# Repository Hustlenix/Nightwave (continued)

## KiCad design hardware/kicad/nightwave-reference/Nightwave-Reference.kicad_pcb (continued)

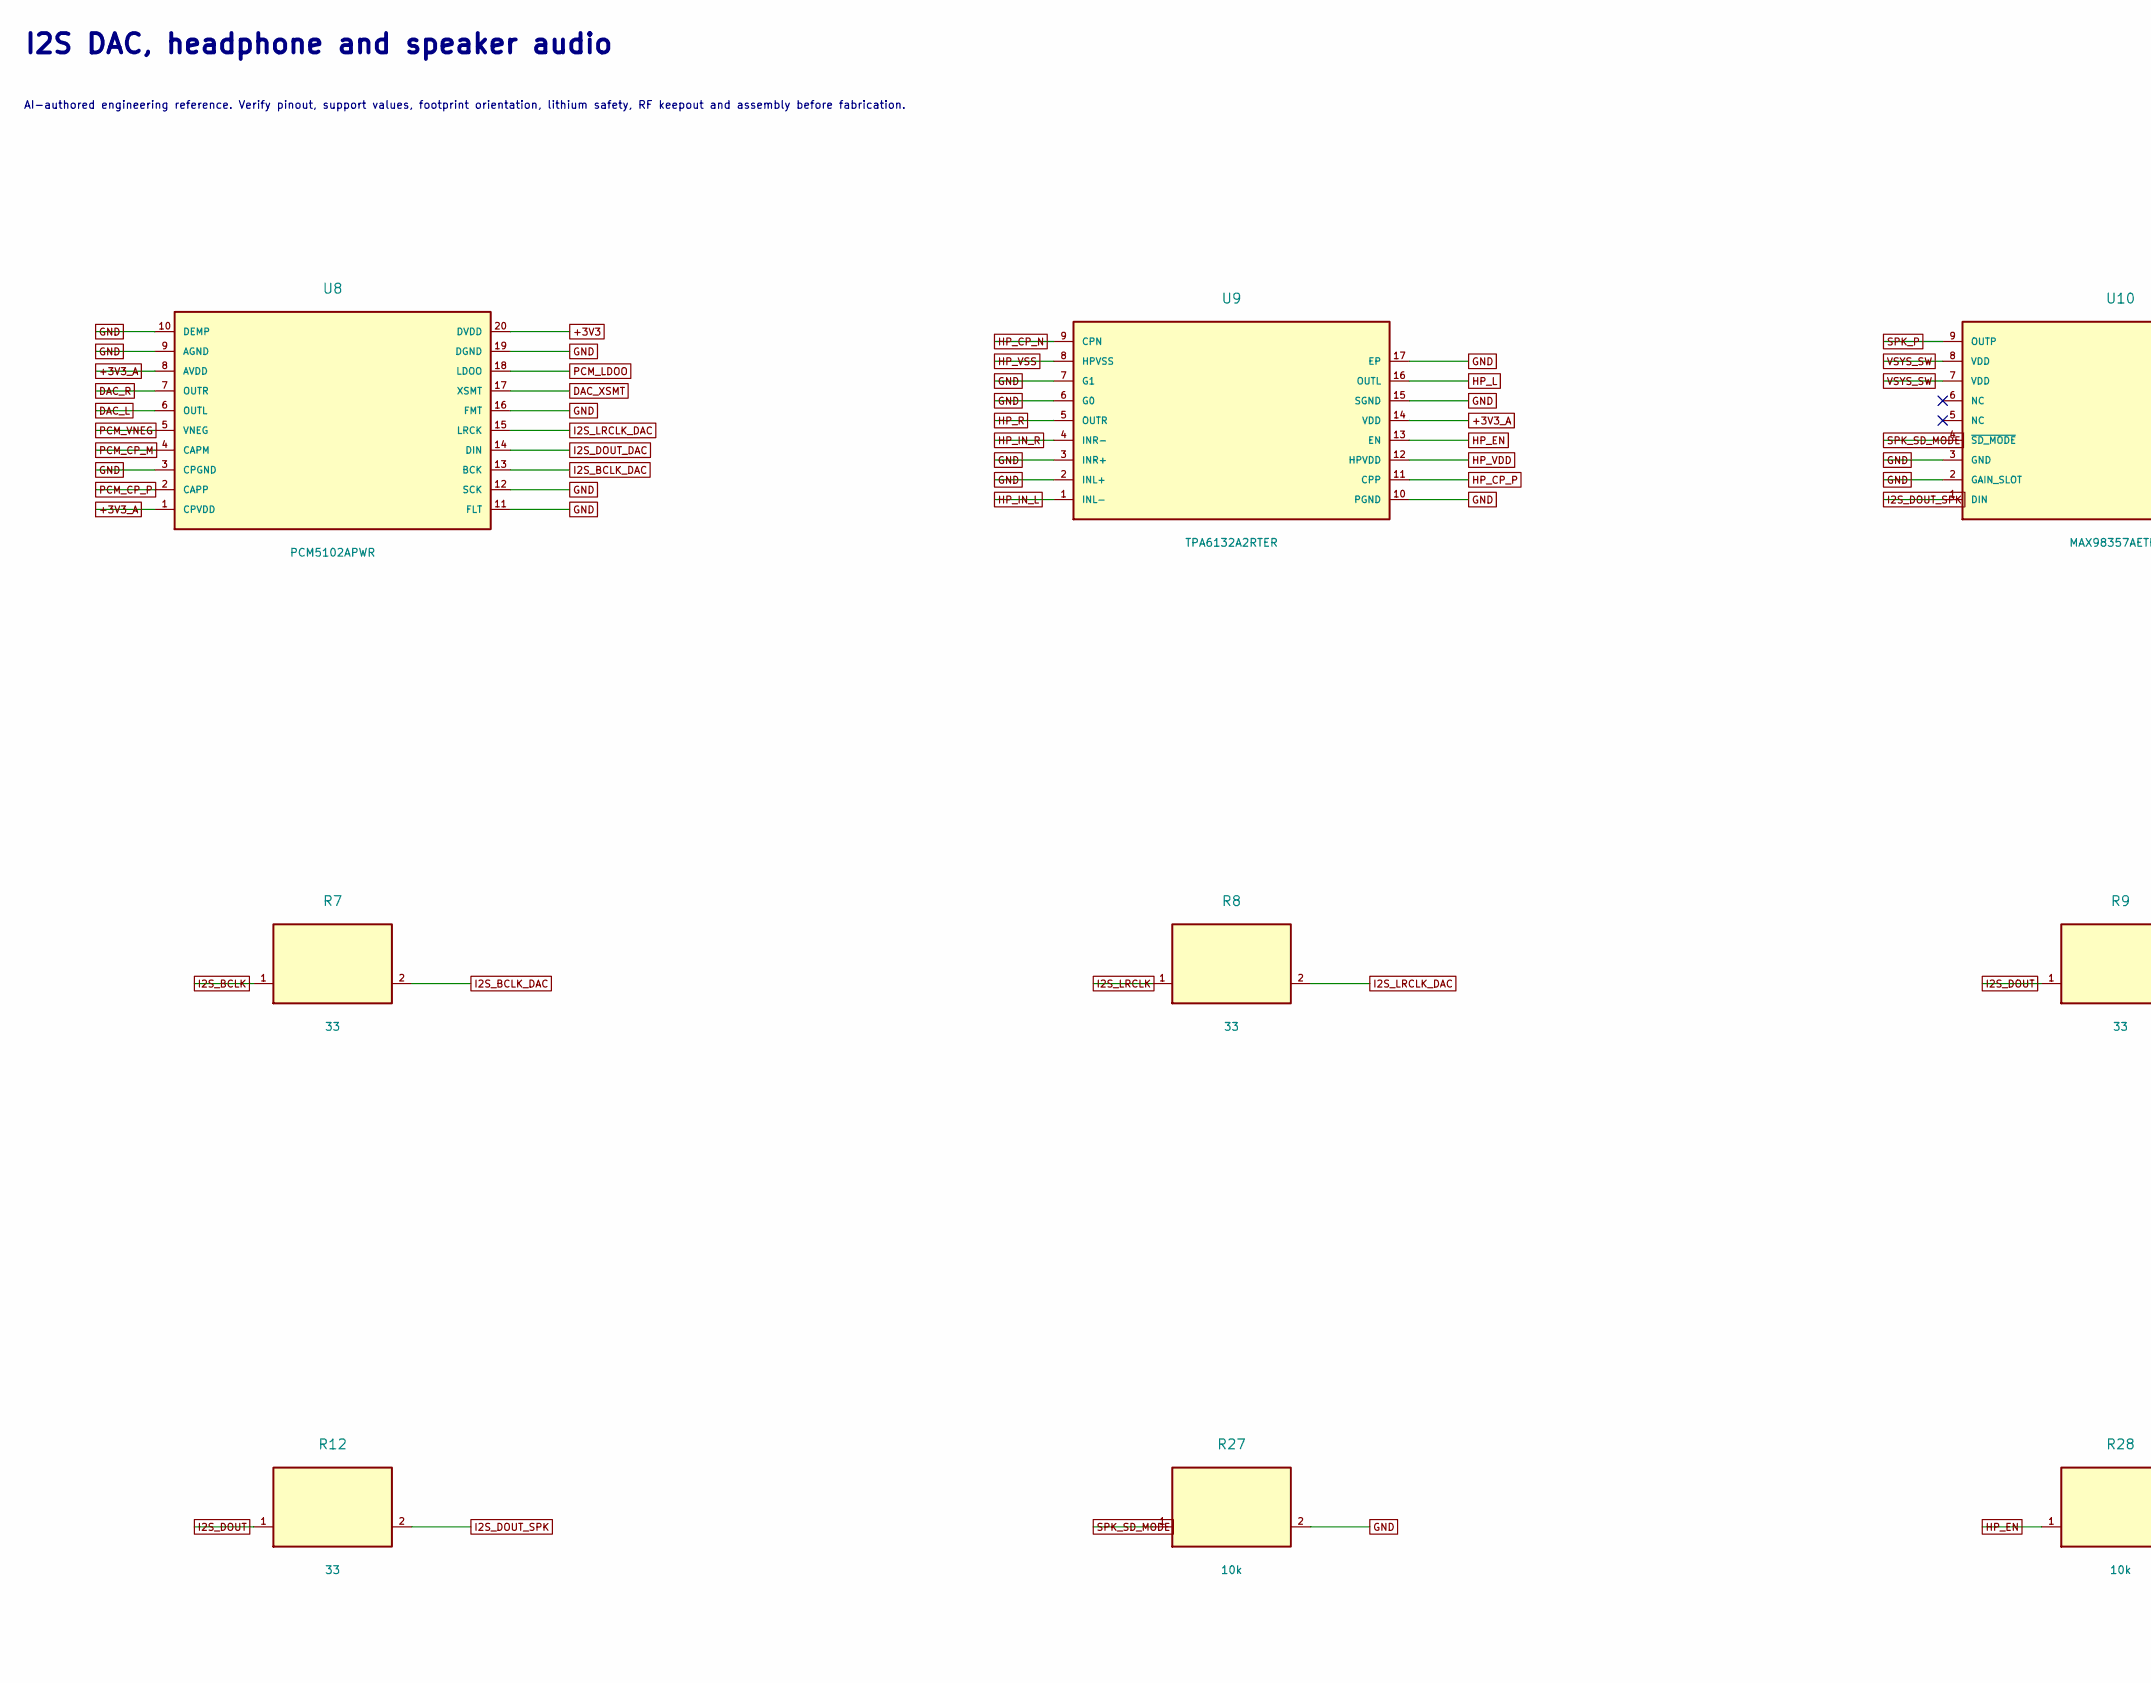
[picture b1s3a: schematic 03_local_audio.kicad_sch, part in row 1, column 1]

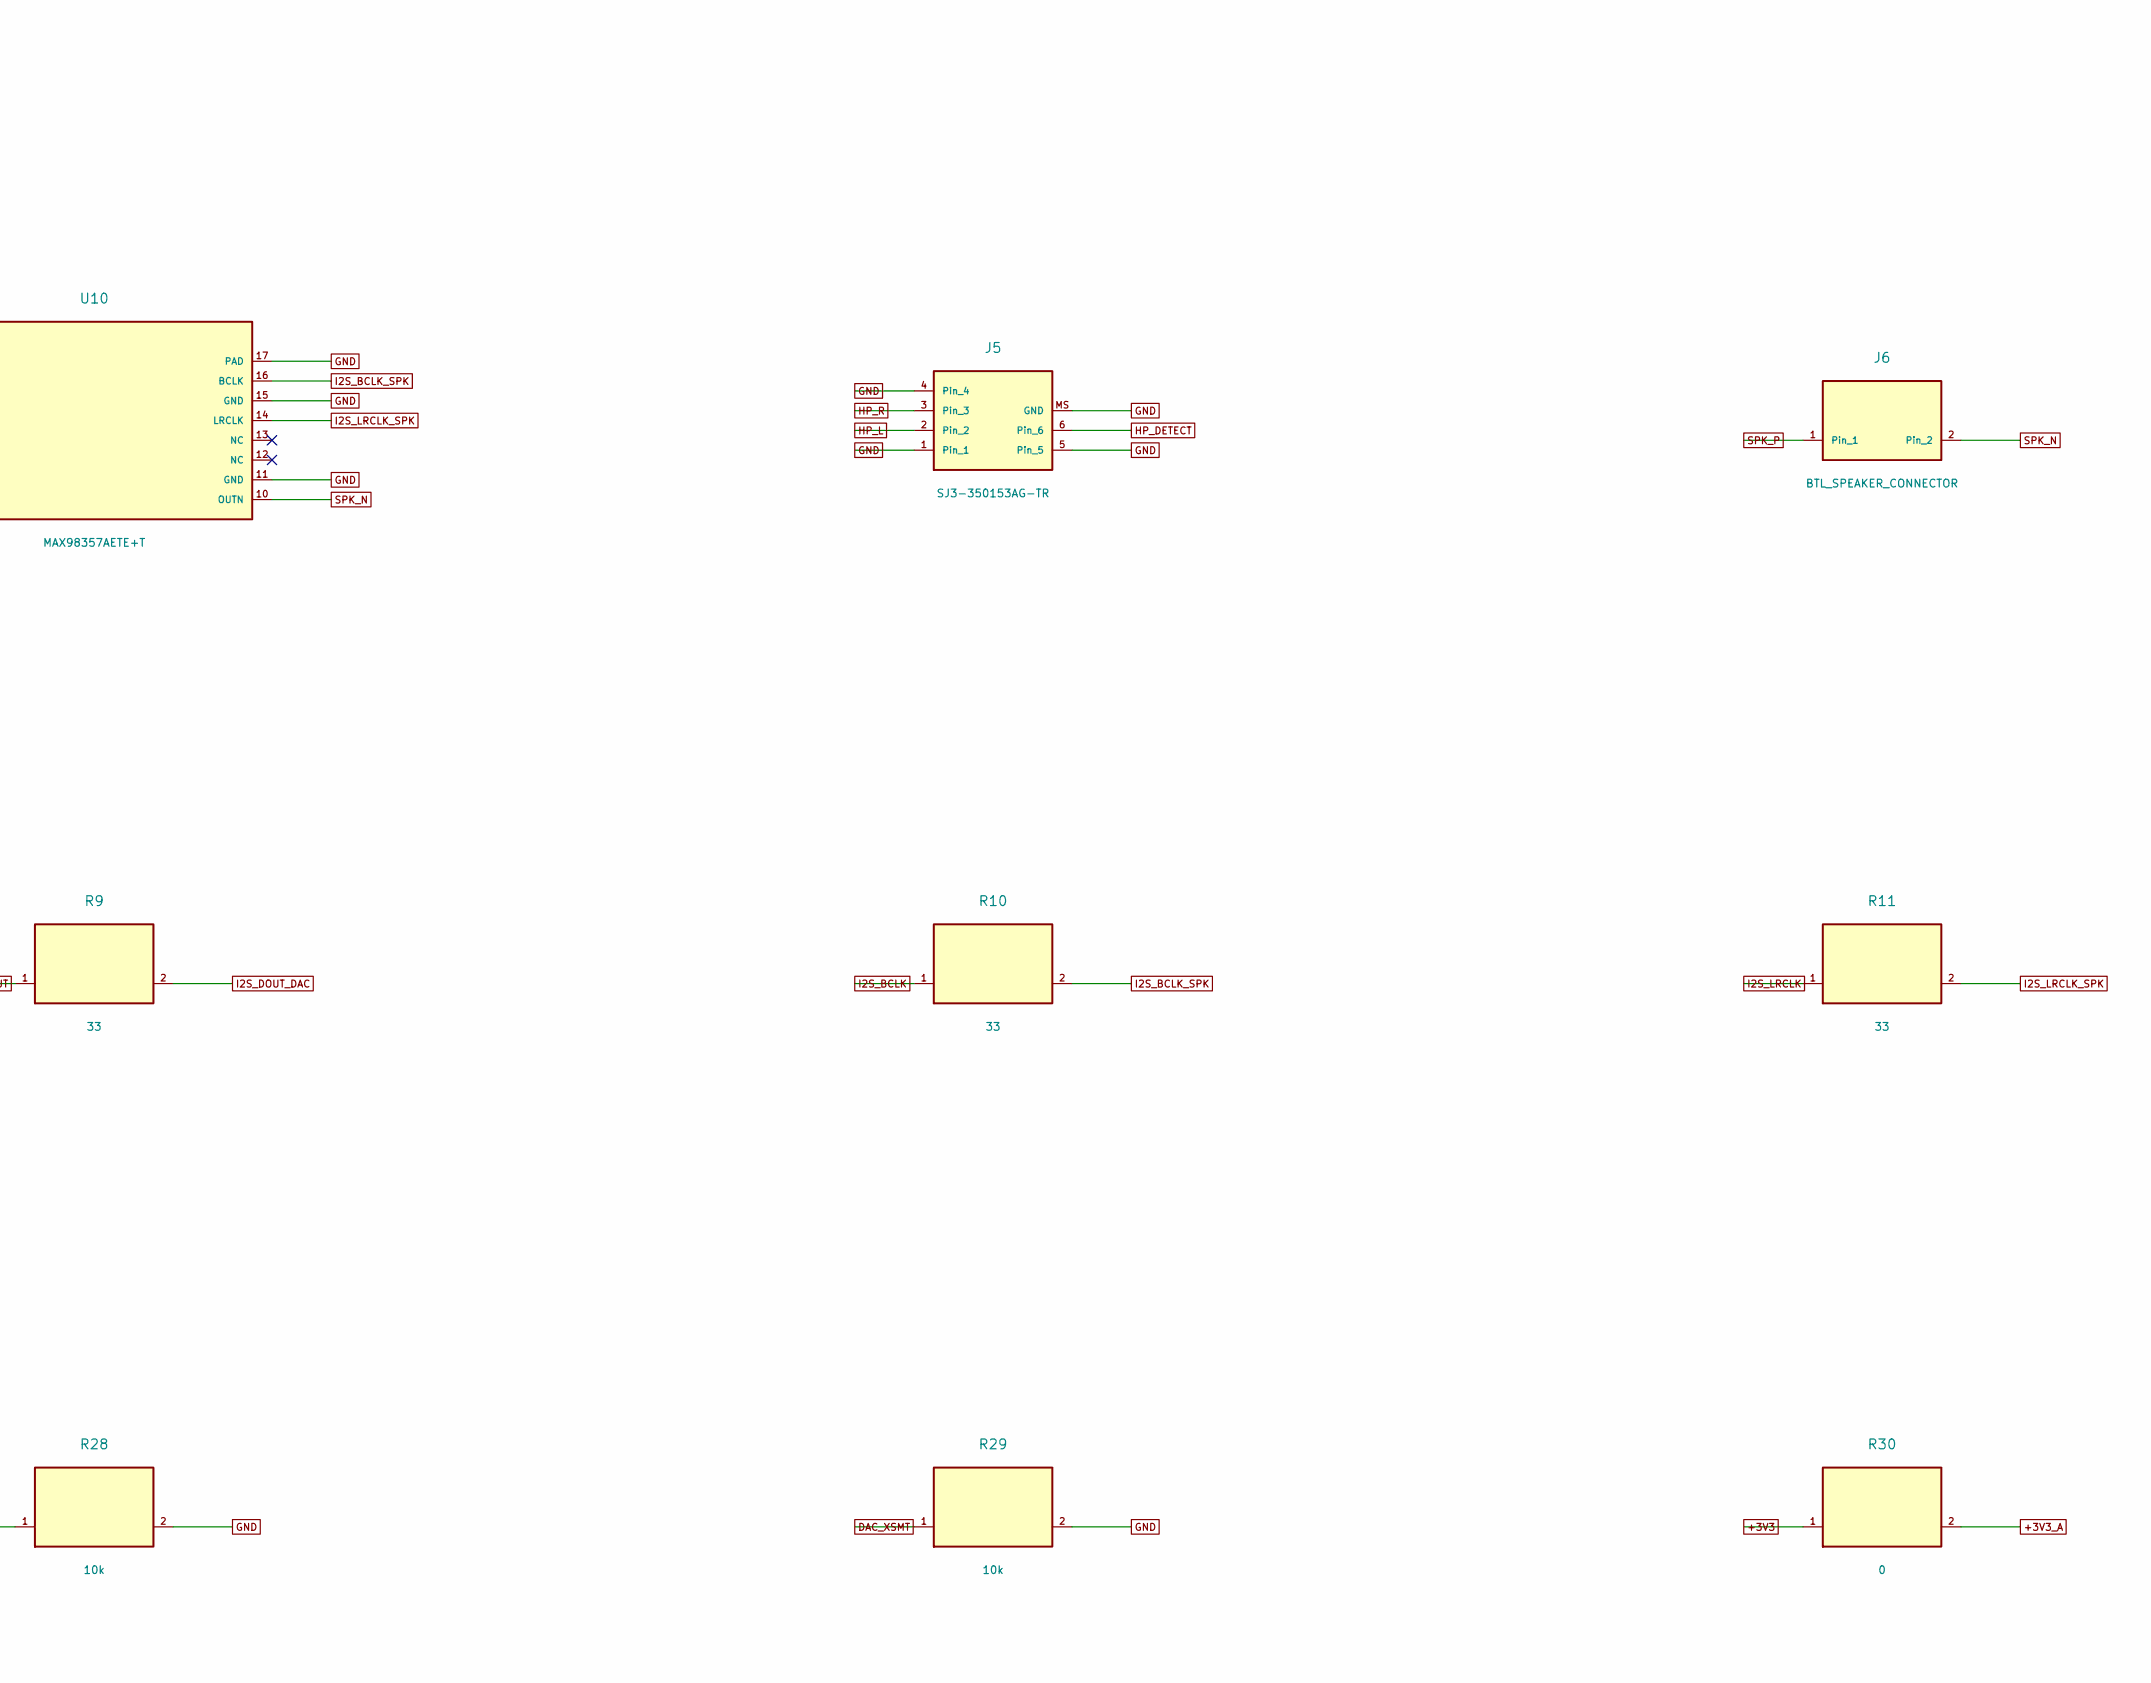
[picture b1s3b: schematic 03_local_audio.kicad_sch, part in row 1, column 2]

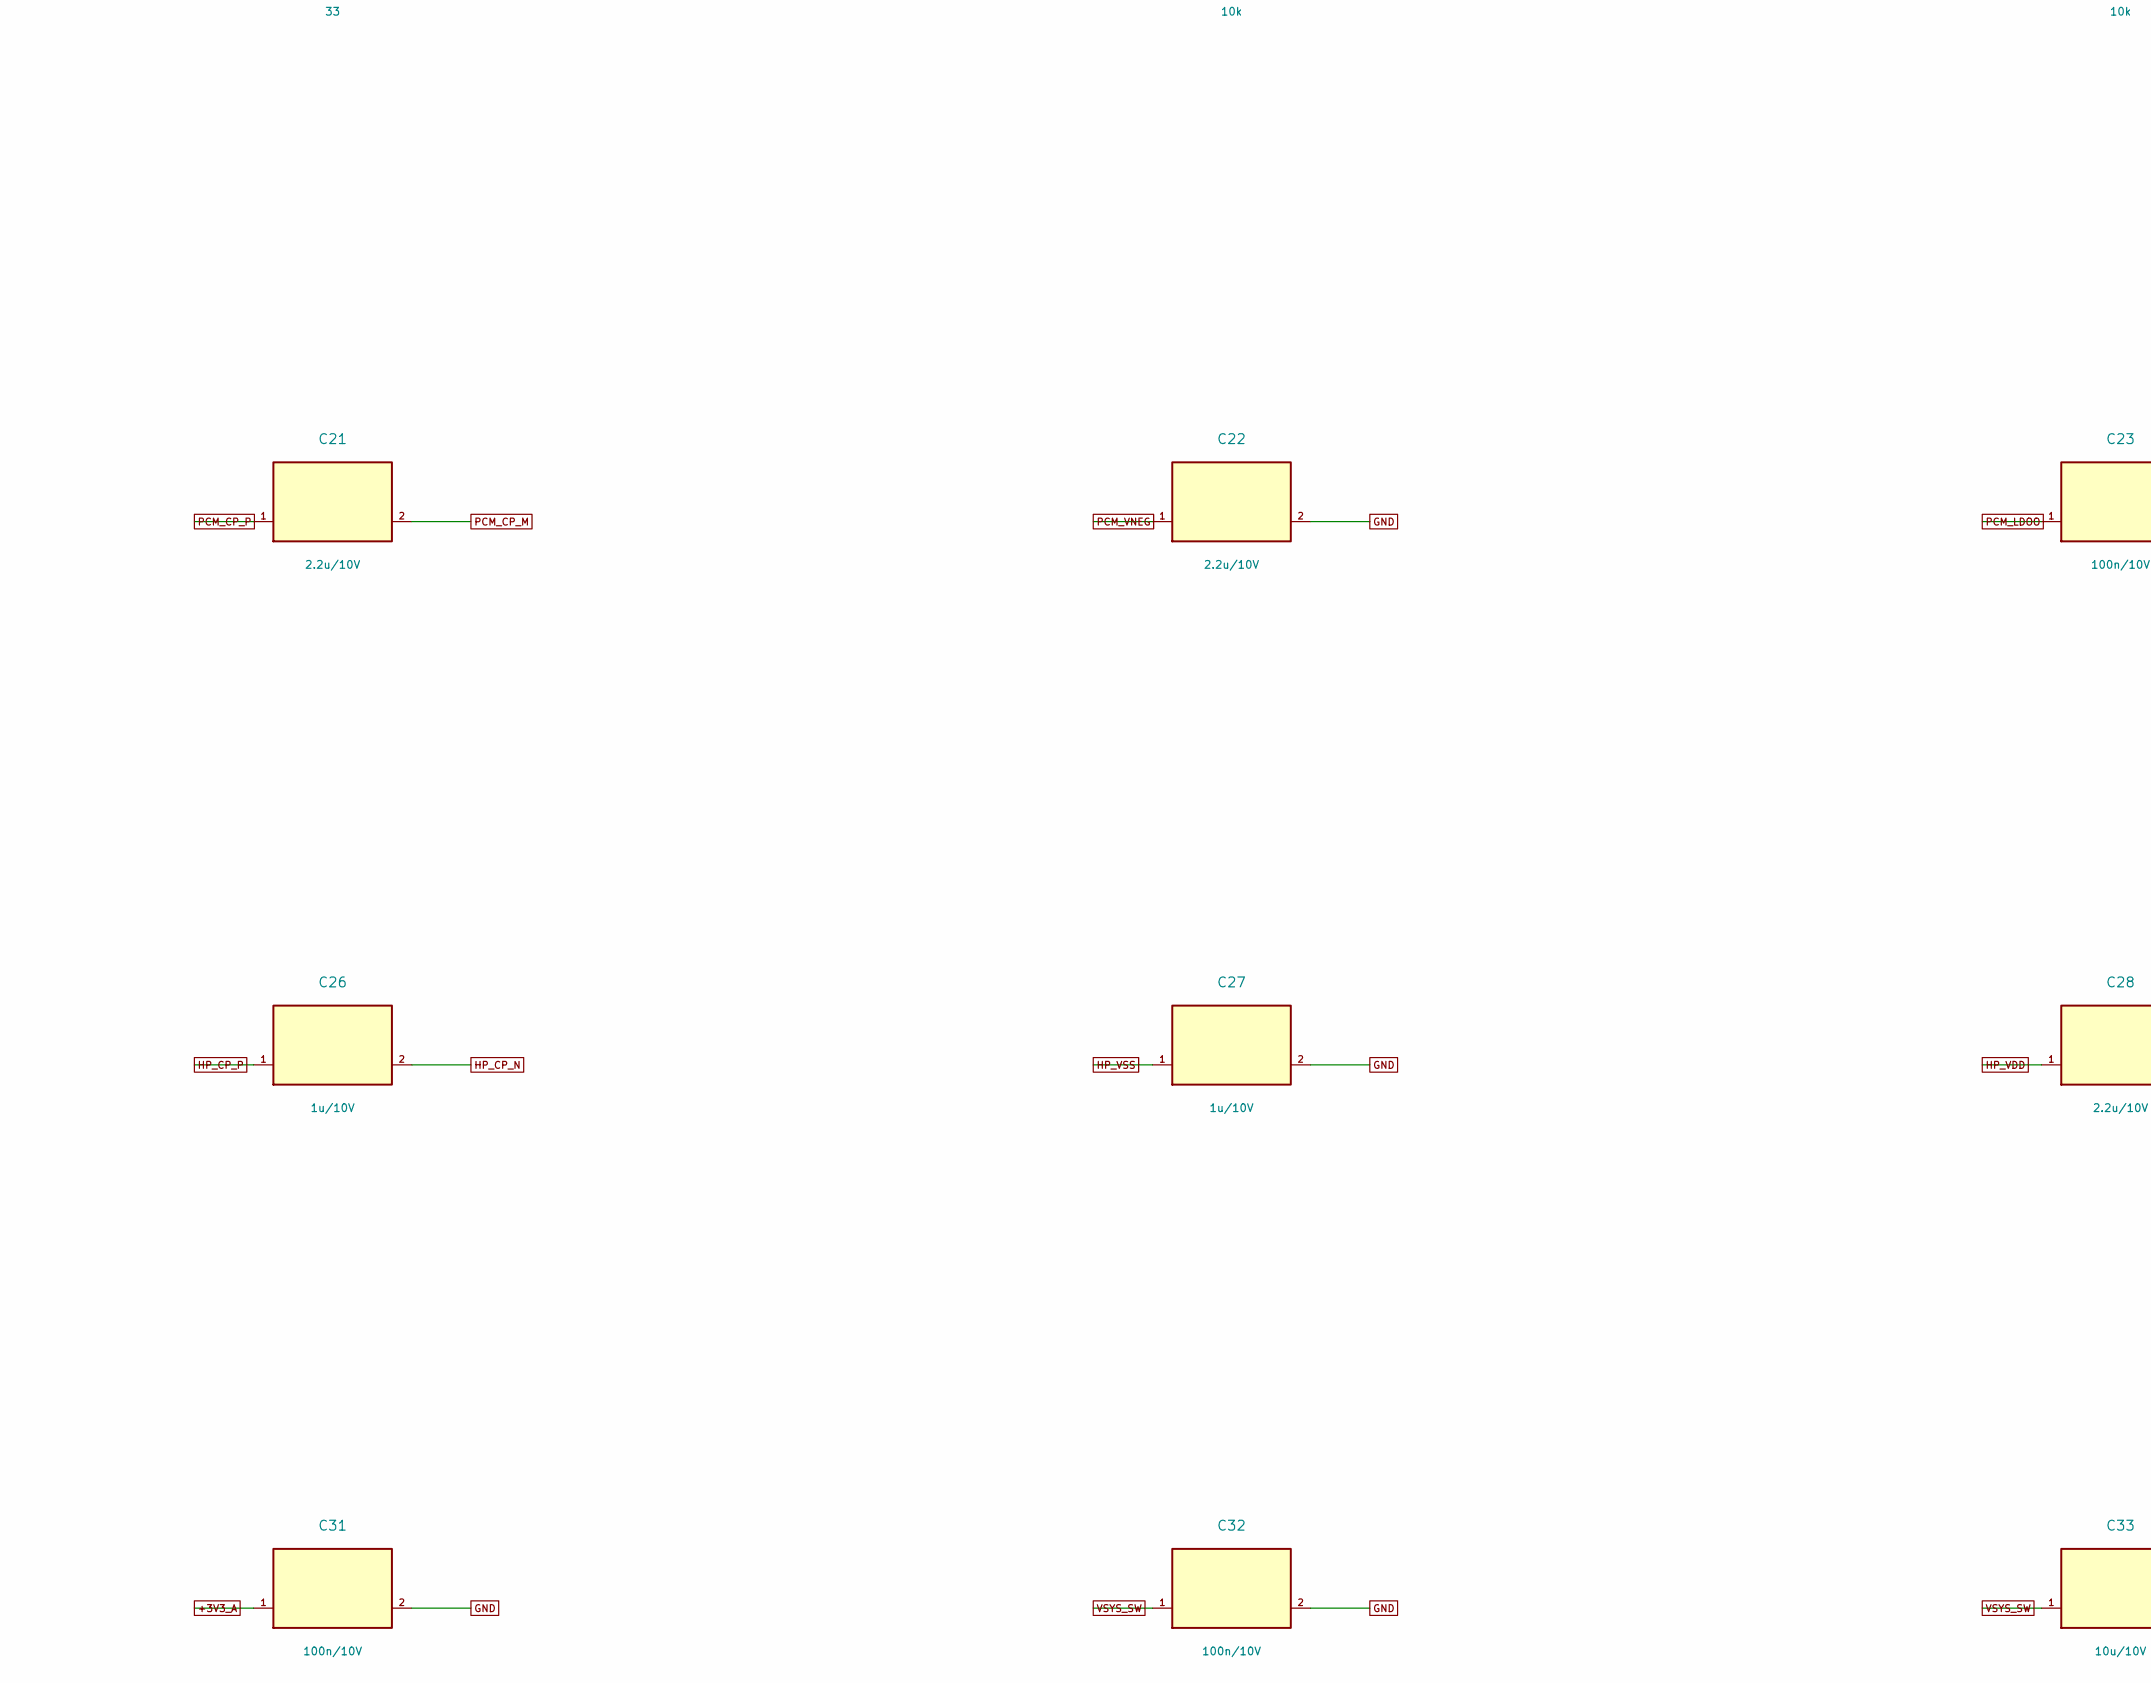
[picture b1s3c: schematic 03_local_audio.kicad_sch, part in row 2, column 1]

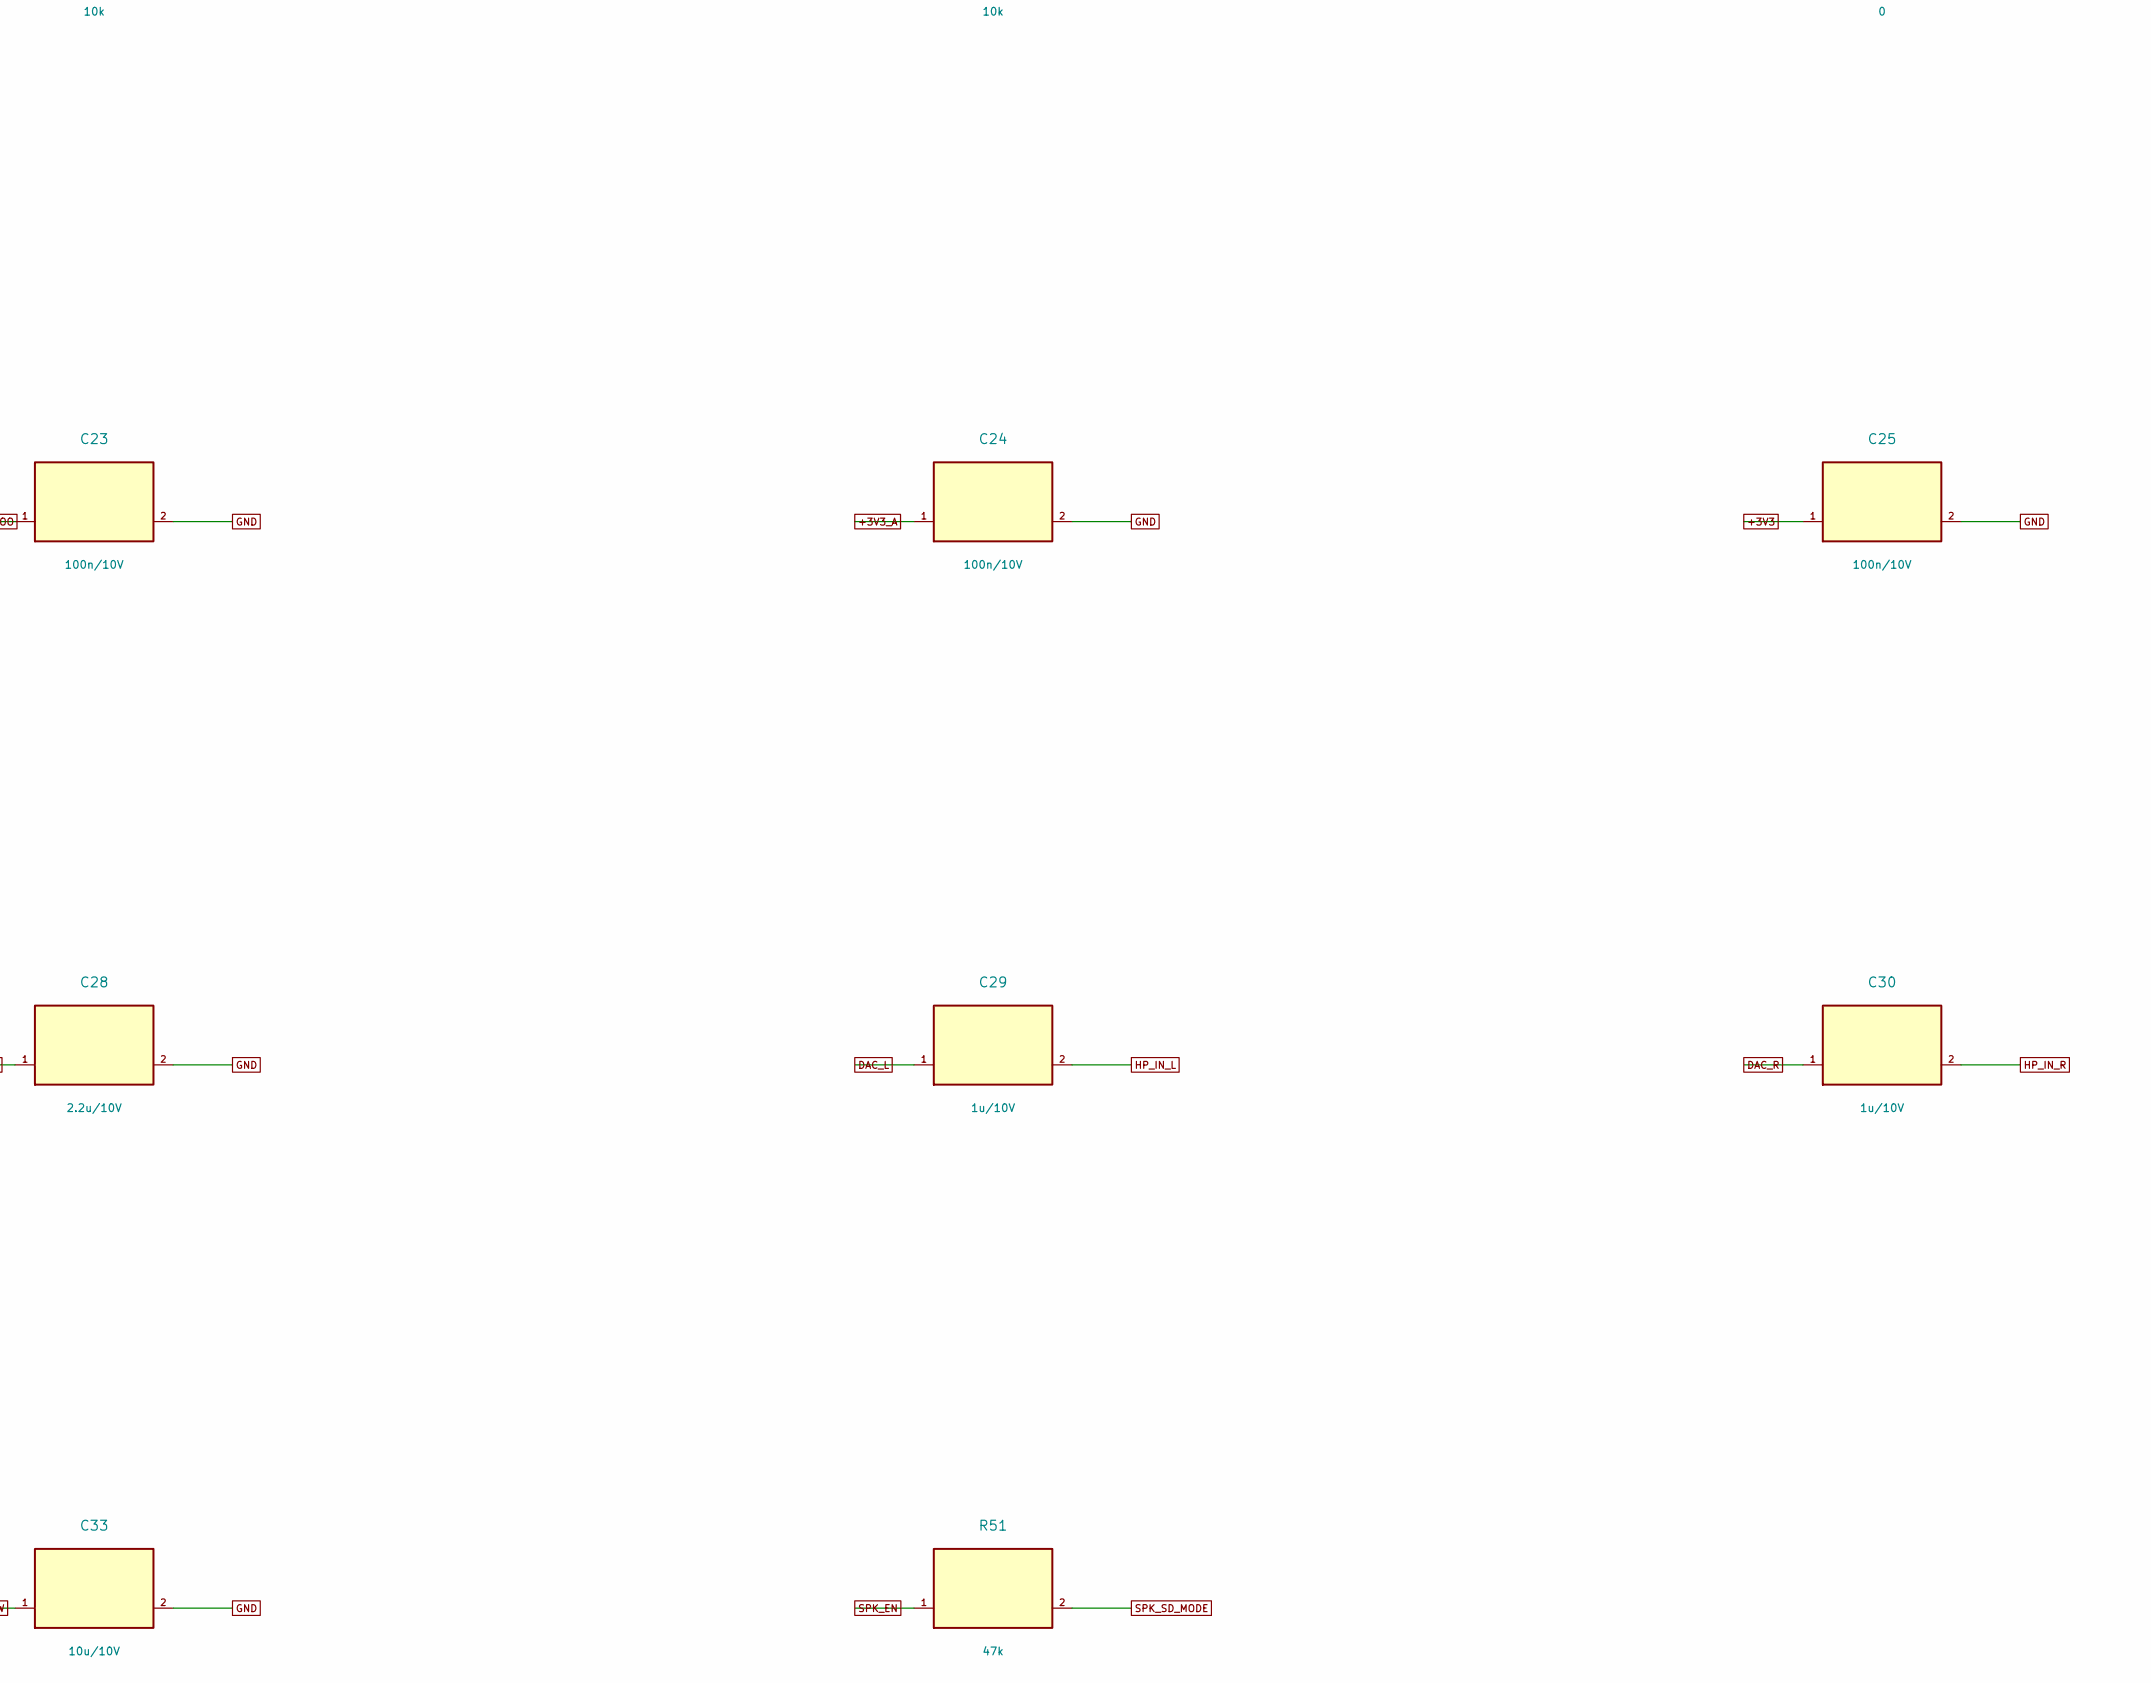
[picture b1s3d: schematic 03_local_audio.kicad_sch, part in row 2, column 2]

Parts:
C21, C22, C28: 2.2u/10V; C_0805_2012Metric
C23, C24, C25, C31, C32: 100n/10V; C_0805_2012Metric
C26, C27, C29, C30: 1u/10V; C_0805_2012Metric
C33: 10u/10V; C_0805_2012Metric
J5: SJ3-350153AG-TR; SameSky_SJ3-350153AG
J6: BTL_SPEAKER_CONNECTOR; JST_PH_S2B-PH-K_1x02_P2.00mm_Horizontal
R7, R8, R9, R10, R11, R12: 33; R_0603_1608Metric
R27, R28, R29: 10k; R_0603_1608Metric
R30: 0; R_0603_1608Metric
R51: 47k; R_0603_1608Metric
U8: PCM5102APWR; Texas_PW0020A_TSSOP-20_4.4x6.5mm_P0.65mm
U9: TPA6132A2RTER; VQFN-16-1EP_3x3mm_P0.5mm_EP1.6x1.6mm_ThermalVias
U10: MAX98357AETE+T; TQFN-16-1EP_3x3mm_P0.5mm_EP1.23x1.23mm

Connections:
+3V3: C25.1 (+3V3), R30.1 (+3V3), U8.20 (DVDD); also elsewhere on the board
+3V3_A: C24.1 (+3V3_A), C31.1 (+3V3_A), R30.2 (+3V3_A), U8.1 (CPVDD), U8.8 (AVDD), U9.14 (VDD); also elsewhere on the board
DAC_L: C29.1 (DAC_L), U8.6 (OUTL)
DAC_R: C30.1 (DAC_R), U8.7 (OUTR)
DAC_XSMT: R29.1 (DAC_XSMT), U8.17 (XSMT); also elsewhere on the board
GND: C22.2 (GND), C23.2 (GND), C24.2 (GND), C25.2 (GND), C27.2 (GND), C28.2 (GND), C31.2 (GND), C32.2 (GND), C33.2 (GND), J5.1, J5.4, J5.5, J5.MS (GND), R27.2 (GND), R28.2 (GND), R29.2 (GND), U8.3 (CPGND), U8.9 (AGND), U8.10 (DEMP), U8.11 (FLT), U8.12 (SCK), U8.16 (FMT), U8.19 (DGND), U9.2 (INL+), U9.3 (INR+), U9.6 (G0), U9.7 (G1), U9.10 (PGND), U9.15 (SGND), U9.17 (EP), U10.2 (GAIN_SLOT), U10.3 (GND), U10.11 (GND), U10.15 (GND), U10.17 (PAD); also elsewhere on the board
HP_CP_N: C26.2 (HP_CP_N), U9.9 (CPN)
HP_CP_P: C26.1 (HP_CP_P), U9.11 (CPP)
HP_DETECT: J5.6; also elsewhere on the board
HP_EN: R28.1 (HP_EN), U9.13 (EN); also elsewhere on the board
HP_IN_L: C29.2 (HP_IN_L), U9.1 (INL-)
HP_IN_R: C30.2 (HP_IN_R), U9.4 (INR-)
HP_L: J5.2, U9.16 (OUTL)
HP_R: J5.3, U9.5 (OUTR)
HP_VDD: C28.1 (HP_VDD), U9.12 (HPVDD)
HP_VSS: C27.1 (HP_VSS), U9.8 (HPVSS)
I2S_BCLK: R7.1 (I2S_BCLK), R10.1 (I2S_BCLK); also elsewhere on the board
I2S_BCLK_DAC: R7.2 (I2S_BCLK_DAC), U8.13 (BCK)
I2S_BCLK_SPK: R10.2 (I2S_BCLK_SPK), U10.16 (BCLK)
I2S_DOUT: R9.1 (I2S_DOUT), R12.1 (I2S_DOUT); also elsewhere on the board
I2S_DOUT_DAC: R9.2 (I2S_DOUT_DAC), U8.14 (DIN)
I2S_DOUT_SPK: R12.2 (I2S_DOUT_SPK), U10.1 (DIN)
I2S_LRCLK: R8.1 (I2S_LRCLK), R11.1 (I2S_LRCLK); also elsewhere on the board
I2S_LRCLK_DAC: R8.2 (I2S_LRCLK_DAC), U8.15 (LRCK)
I2S_LRCLK_SPK: R11.2 (I2S_LRCLK_SPK), U10.14 (LRCLK)
PCM_CP_M: C21.2 (PCM_CP_M), U8.4 (CAPM)
PCM_CP_P: C21.1 (PCM_CP_P), U8.2 (CAPP)
PCM_LDOO: C23.1 (PCM_LDOO), U8.18 (LDOO)
PCM_VNEG: C22.1 (PCM_VNEG), U8.5 (VNEG)
SPK_EN: R51.1 (SPK_EN); also elsewhere on the board
SPK_N: J6.2, U10.10 (OUTN)
SPK_P: J6.1, U10.9 (OUTP)
SPK_SD_MODE: R27.1 (SPK_SD_MODE), R51.2 (SPK_SD_MODE), U10.4 (~SD_MODE)
VSYS_SW: C32.1 (VSYS_SW), C33.1 (VSYS_SW), U10.7 (VDD), U10.8 (VDD); also elsewhere on the board

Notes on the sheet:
I2S DAC, headphone and speaker audio
AI-authored engineering reference. Verify pinout, support values, footprint orientation, lithium safety, RF keepout and assembly before fabrication.
